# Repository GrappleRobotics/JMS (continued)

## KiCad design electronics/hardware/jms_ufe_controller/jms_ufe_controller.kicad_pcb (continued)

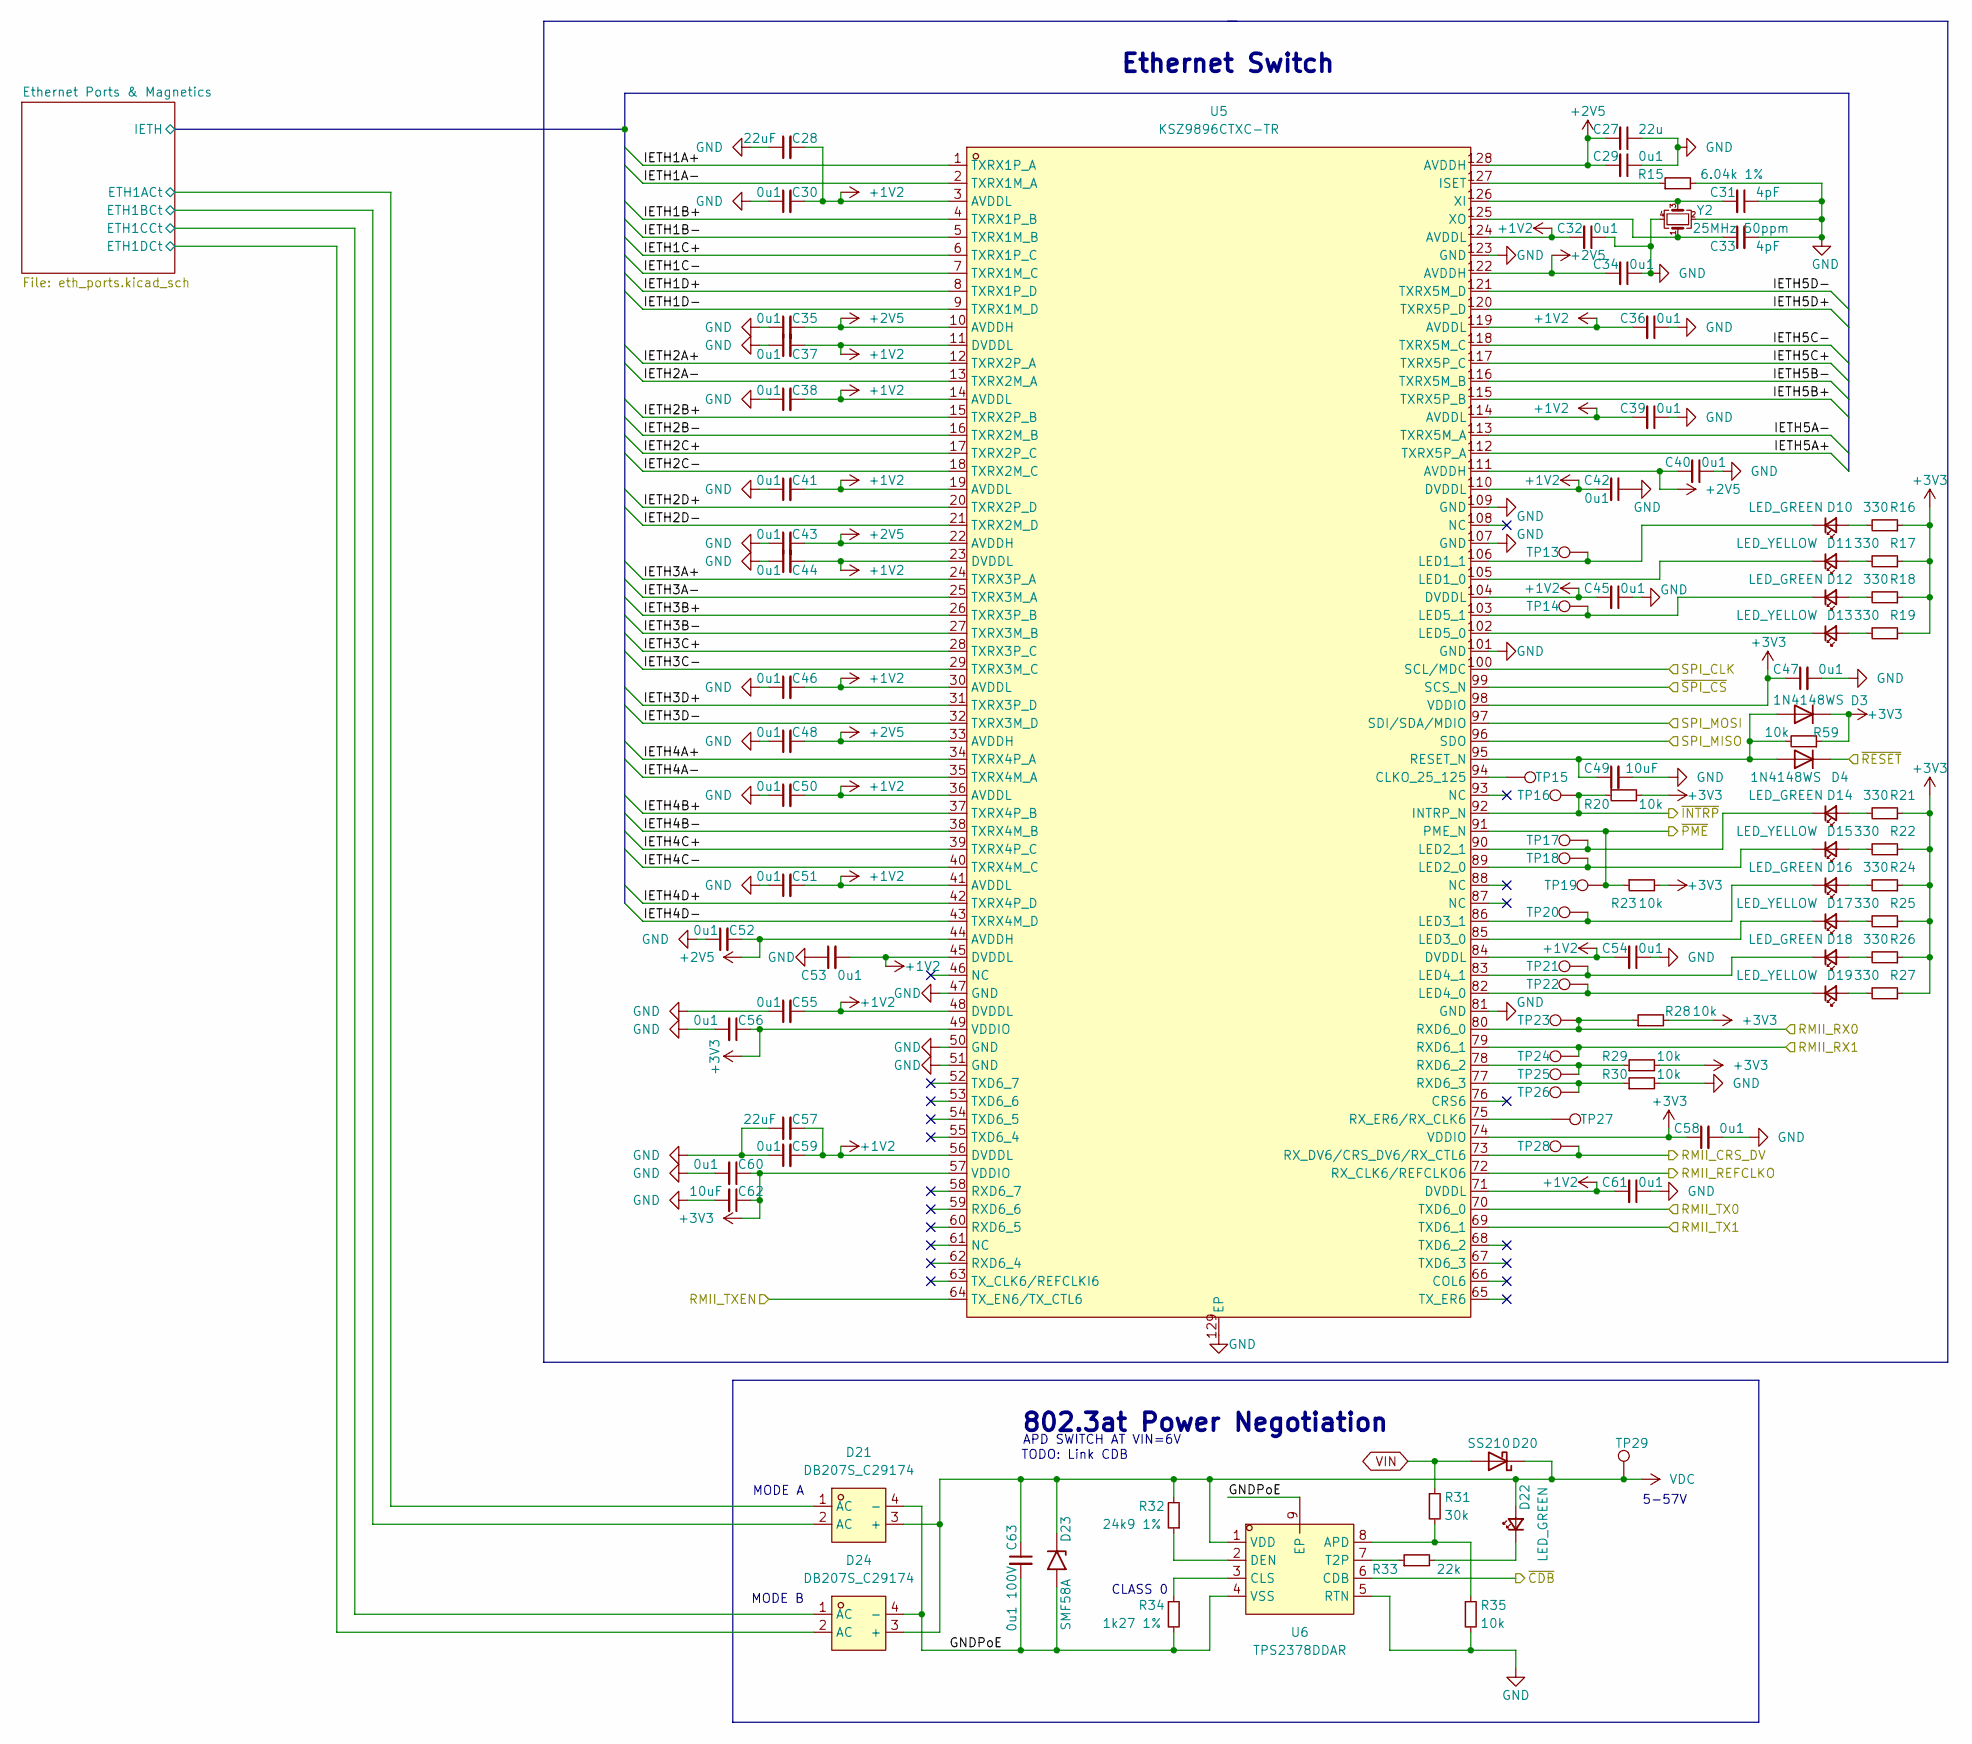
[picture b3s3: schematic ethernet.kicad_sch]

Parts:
C27: 22u; C_0402_1005Metric
C28, C57: 22uF; C_0402_1005Metric
C29, C30, C32, C34, C35, C36, C37, C38, C39, C40, C41, C42, C43, C44, C45, C46, C47, C48, C50, C51, C52, C53, C54, C55, C56, C58, C59, C60, C61: 0u1; C_0402_1005Metric
C31, C33: 4pF; C_0402_1005Metric
C49, C62: 10uF; C_0402_1005Metric
C63: 0u1 100V; C_0805_2012Metric; LCSC C28233
D3, D4: 1N4148WS; D_SOD-323
D10, D12, D14, D16, D18, D22: LED_GREEN; LED_0603_1608Metric; LCSC C72043
D11, D13, D15, D17, D19: LED_YELLOW; LED_0603_1608Metric; LCSC C72038
D20: SS210; D_SMA; LCSC C14996
D21, D24: DB207S_C29174; DBS_L8.4-W6.4-P5.10-LS10.2-TL; LCSC Part C29174
D23: SMF58A; D_SMF
R15: 6.04k 1%; R_0402_1005Metric
R16, R17, R18, R19, R21, R22, R24, R25, R26, R27: 330; R_0402_1005Metric
R20, R23, R28, R29, R30, R35, R59: 10k; R_0402_1005Metric
R31: 30k; R_0402_1005Metric
R32: 24k9 1%; R_0402_1005Metric
R33: 22k; R_0402_1005Metric
R34: 1k27 1%; R_0402_1005Metric
TP13, TP14, TP15, TP16, TP17, TP18, TP19, TP20, TP21, TP22, TP23, TP24, TP25, TP26, TP27, TP28, TP29: TestPoint; TestPoint_Pad_1.5x1.5mm
U5: KSZ9896CTXC-TR; TQFP-128_L14.0-W14.0-P0.40-LS16.0-BL-EP; LCSC Part C631691
U6: TPS2378DDAR; SO-8_L4.9-W3.9-P1.27-LS6.0-BL-EP; LCSC Part C337500
Y2: 25MHz 50ppm; Crystal_SMD_3225-4Pin_3.2x2.5mm; LCSC C9006

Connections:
+1V2: C28.2, C30.2, C32.2, C36.2, C37.2, C38.2, C39.2, C41.2, C42.2, C44.2, C45.2, C46.2, C50.2, C51.2, C53.2, C54.2, C55.2, C57.2, C59.2, C61.2, U5.3 (AVDDL), U5.11 (DVDDL), U5.14 (AVDDL), U5.19 (AVDDL), U5.23 (DVDDL), U5.30 (AVDDL), U5.36 (AVDDL), U5.41 (AVDDL), U5.45 (DVDDL), U5.48 (DVDDL), U5.56 (DVDDL), U5.71 (DVDDL), U5.84 (DVDDL), U5.104 (DVDDL), U5.110 (DVDDL), U5.114 (AVDDL), U5.119 (AVDDL), U5.124 (AVDDL); also elsewhere on the board
+2V5: C27.2, C29.2, C34.2, C35.2, C40.2, C43.2, C48.2, C52.2, U5.10 (AVDDH), U5.22 (AVDDH), U5.33 (AVDDH), U5.44 (AVDDH), U5.111 (AVDDH), U5.122 (AVDDH), U5.128 (AVDDH); also elsewhere on the board
+3V3: C47.1, C56.1, C58.1, C60.1, C62.1, D3.1 (K), R16.1, R17.1, R18.1, R19.1, R20.2, R21.1, R22.1, R23.2, R24.1, R25.1, R26.1, R27.1, R28.2, R29.2, R59.1, U5.49 (VDDIO), U5.57 (VDDIO), U5.74 (VDDIO), U5.98 (VDDIO); also elsewhere on the board
/EH_SPI_SCLK: U5.100 (SCL/MDC)
/ETH_CRS_DV: TP28.1, U5.73 (RX_DV6/CRS_DV6/RX_CTL6); also elsewhere on the board
/ETH_REF_CLK: U5.72 (RX_CLK6/REFCLKO6); also elsewhere on the board
/ETH_RXD0: R28.1, TP23.1, U5.80 (RXD6_0); also elsewhere on the board
/ETH_RXD1: TP24.1, U5.79 (RXD6_1); also elsewhere on the board
/ETH_SPI_CS: U5.99 (SCS_N); also elsewhere on the board
/ETH_SPI_MISO: U5.96 (SDO); also elsewhere on the board
/ETH_SPI_MOSI: U5.97 (SDI/SDA/MDIO); also elsewhere on the board
/ETH_TXD0: U5.70 (TXD6_0); also elsewhere on the board
/ETH_TXD1: U5.69 (TXD6_1); also elsewhere on the board
/ETH_TX_EN: U5.64 (TX_EN6/TX_CTL6); also elsewhere on the board
/ethernet/Ethernet Ports & Magnetics/ETH1ACt: D21.1 (AC); also elsewhere on the board
/ethernet/Ethernet Ports & Magnetics/ETH1BCt: D21.2 (AC); also elsewhere on the board
/ethernet/Ethernet Ports & Magnetics/ETH1CCt: D24.1 (AC); also elsewhere on the board
/ethernet/Ethernet Ports & Magnetics/ETH1DCt: D24.2 (AC); also elsewhere on the board
/ethernet/GNDPoE: C63.2, D21.4 (-), D23.2 (A2), D24.4 (-), R34.2, U6.4 (VSS), U6.9 (EP)
/ethernet/IETH1A+: U5.1 (TXRX1P_A)
/ethernet/IETH1A-: U5.2 (TXRX1M_A)
/ethernet/IETH1B+: U5.4 (TXRX1P_B)
/ethernet/IETH1B-: U5.5 (TXRX1M_B)
/ethernet/IETH1C+: U5.6 (TXRX1P_C)
/ethernet/IETH1C-: U5.7 (TXRX1M_C)
/ethernet/IETH1D+: U5.8 (TXRX1P_D)
/ethernet/IETH1D-: U5.9 (TXRX1M_D)
/ethernet/IETH2A+: U5.12 (TXRX2P_A)
/ethernet/IETH2A-: U5.13 (TXRX2M_A)
/ethernet/IETH2B+: U5.15 (TXRX2P_B)
/ethernet/IETH2B-: U5.16 (TXRX2M_B)
/ethernet/IETH2C+: U5.17 (TXRX2P_C)
/ethernet/IETH2C-: U5.18 (TXRX2M_C)
/ethernet/IETH2D+: U5.20 (TXRX2P_D)
/ethernet/IETH2D-: U5.21 (TXRX2M_D)
/ethernet/IETH3A+: U5.24 (TXRX3P_A)
/ethernet/IETH3A-: U5.25 (TXRX3M_A)
/ethernet/IETH3B+: U5.26 (TXRX3P_B)
/ethernet/IETH3B-: U5.27 (TXRX3M_B)
/ethernet/IETH3C+: U5.28 (TXRX3P_C)
/ethernet/IETH3C-: U5.29 (TXRX3M_C)
/ethernet/IETH3D+: U5.31 (TXRX3P_D)
/ethernet/IETH3D-: U5.32 (TXRX3M_D)
/ethernet/IETH4A+: U5.34 (TXRX4P_A)
/ethernet/IETH4A-: U5.35 (TXRX4M_A)
/ethernet/IETH4B+: U5.37 (TXRX4P_B)
/ethernet/IETH4B-: U5.38 (TXRX4M_B)
/ethernet/IETH4C+: U5.39 (TXRX4P_C)
/ethernet/IETH4C-: U5.40 (TXRX4M_C)
/ethernet/IETH4D+: U5.42 (TXRX4P_D)
/ethernet/IETH4D-: U5.43 (TXRX4M_D)
/ethernet/IETH5A+: U5.112 (TXRX5P_A)
/ethernet/IETH5A-: U5.113 (TXRX5M_A)
/ethernet/IETH5B+: U5.115 (TXRX5P_B)
/ethernet/IETH5B-: U5.116 (TXRX5M_B)
/ethernet/IETH5C+: U5.117 (TXRX5P_C)
/ethernet/IETH5C-: U5.118 (TXRX5M_C)
/ethernet/IETH5D+: U5.120 (TXRX5P_D)
/ethernet/IETH5D-: U5.121 (TXRX5M_D)
/ethernet/~CDB: U6.6 (CDB); also elsewhere on the board
/~ETH_INTERRUPT: R20.1, TP16.1, U5.92 (INTRP_N); also elsewhere on the board
/~ETH_PME: R23.1, TP19.1, U5.91 (PME_N); also elsewhere on the board
/~ETH_RESET: D4.1 (K); also elsewhere on the board
GND: C27.1, C28.1, C29.1, C30.1, C31.1, C32.1, C33.2, C34.1, C35.1, C36.1, C37.1, C38.1, C39.1, C40.1, C41.1, C42.1, C43.1, C44.1, C45.1, C46.1, C47.2, C48.1, C49.2, C50.1, C51.1, C52.1, C53.1, C54.1, C55.1, C56.2, C57.1, C58.2, C59.1, C60.2, C61.1, C62.2, R15.2, R30.2, R35.2, U5.47 (GND), U5.50 (GND), U5.51 (GND), U5.81 (GND), U5.101 (GND), U5.107 (GND), U5.109 (GND), U5.123 (GND), U5.129 (EP), U6.5 (RTN), Y2.2, Y2.4; also elsewhere on the board
unnamed: C31.2, U5.126 (XI), Y2.3
unnamed: C33.1, U5.125 (XO), Y2.1
unnamed: C49.1, D3.2 (A), D4.2 (A), R59.2, U5.95 (RESET_N)
unnamed: D10.1 (K), TP13.1, U5.106 (LED1_1)
unnamed: D10.2 (A), R16.2
unnamed: D11.1 (K), U5.105 (LED1_0)
unnamed: D11.2 (A), R17.2
unnamed: D12.1 (K), TP14.1, U5.103 (LED5_1)
unnamed: D12.2 (A), R18.2
unnamed: D13.1 (K), U5.102 (LED5_0)
unnamed: D13.2 (A), R19.2
unnamed: D14.1 (K), TP17.1, U5.90 (LED2_1)
unnamed: D14.2 (A), R21.2
unnamed: D15.1 (K), TP18.1, U5.89 (LED2_0)
unnamed: D15.2 (A), R22.2
unnamed: D16.1 (K), TP20.1, U5.86 (LED3_1)
unnamed: D16.2 (A), R24.2
unnamed: D17.1 (K), U5.85 (LED3_0)
unnamed: D17.2 (A), R25.2
unnamed: D18.1 (K), TP21.1, U5.83 (LED4_1)
unnamed: D18.2 (A), R26.2
unnamed: D19.1 (K), TP22.1, U5.82 (LED4_0)
unnamed: D19.2 (A), R27.2
unnamed: D22.1 (K), R33.2
unnamed: R15.1, U5.127 (ISET)
unnamed: R29.1, TP25.1, U5.78 (RXD6_2)
unnamed: R30.1, TP26.1, U5.77 (RXD6_3)
unnamed: R31.2, R35.1, U6.8 (APD)
unnamed: R32.1, U6.2 (DEN)
unnamed: R33.1, U6.7 (T2P)
unnamed: R34.1, U6.3 (CLS)
unnamed: TP15.1, U5.94 (CLKO_25_125)
unnamed: TP27.1, U5.75 (RX_ER6/RX_CLK6)
VDC: C63.1, D20.1 (K), D21.3 (+), D22.2 (A), D23.1 (A1), D24.3 (+), R32.2, TP29.1, U6.1 (VDD); also elsewhere on the board
VIN: D20.2 (A), R31.1; also elsewhere on the board

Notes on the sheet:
Ethernet Switch
5-57V
TODO: Link CDB
MODE B
MODE A
APD SWITCH AT VIN=6V
CLASS 0
802.3at Power Negotiation

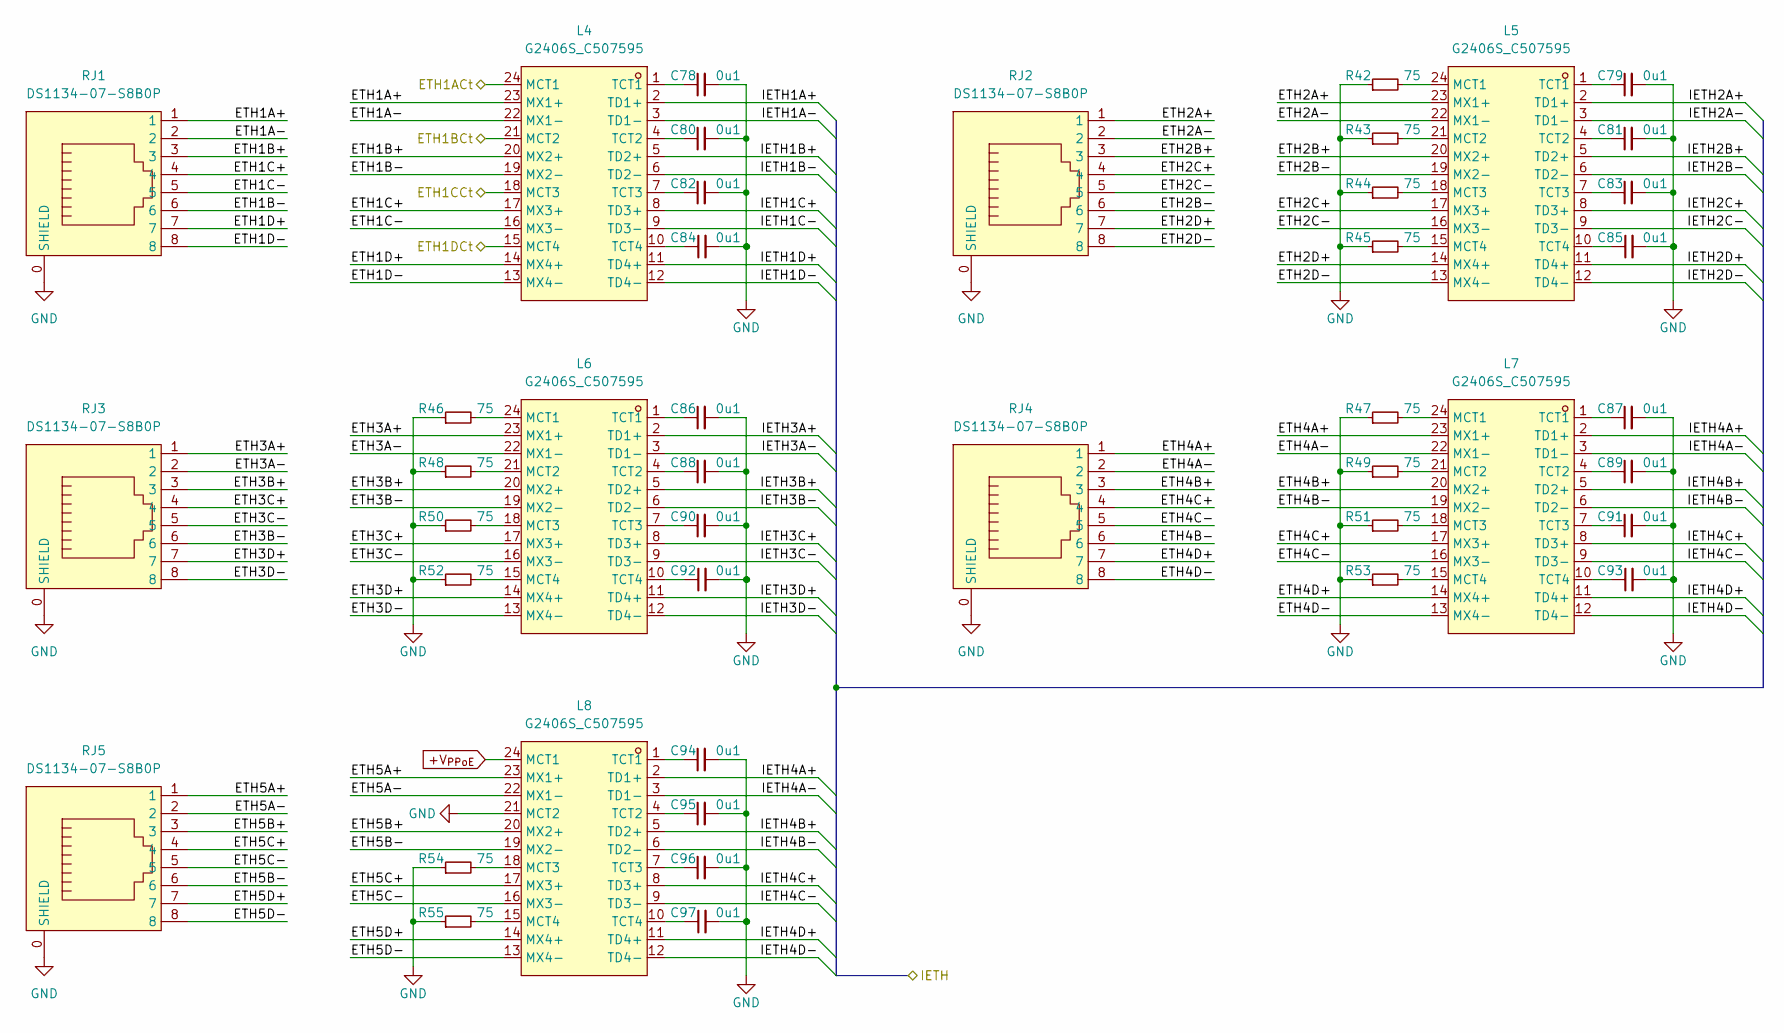
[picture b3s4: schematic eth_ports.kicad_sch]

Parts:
C78, C79, C80, C81, C82, C83, C84, C85, C86, C87, C88, C89, C90, C91, C92, C93, C94, C95, C96, C97: 0u1; C_0402_1005Metric
L4, L5, L6, L7, L8: G2406S_C507595; SMD-24_L15.1-W7.1-P1.00-LS10.0-BL; LCSC Part C507595
R42, R43, R44, R45, R46, R47, R48, R49, R50, R51, R52, R53, R54, R55: 75; R_0402_1005Metric
RJ1, RJ2, RJ3, RJ4, RJ5: DS1134-07-S8B0P; RJ45-TH_DS1134-07-S8B0P; LCSC Part C86579

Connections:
+V_{PPoE}: L8.24 (MCT1); also elsewhere on the board
/ethernet/Ethernet Ports & Magnetics/ETH1A+: L4.23 (MX1+), RJ1.1
/ethernet/Ethernet Ports & Magnetics/ETH1A-: L4.22 (MX1-), RJ1.2
/ethernet/Ethernet Ports & Magnetics/ETH1ACt: L4.24 (MCT1); also elsewhere on the board
/ethernet/Ethernet Ports & Magnetics/ETH1B+: L4.20 (MX2+), RJ1.3
/ethernet/Ethernet Ports & Magnetics/ETH1B-: L4.19 (MX2-), RJ1.6
/ethernet/Ethernet Ports & Magnetics/ETH1BCt: L4.21 (MCT2); also elsewhere on the board
/ethernet/Ethernet Ports & Magnetics/ETH1C+: L4.17 (MX3+), RJ1.4
/ethernet/Ethernet Ports & Magnetics/ETH1C-: L4.16 (MX3-), RJ1.5
/ethernet/Ethernet Ports & Magnetics/ETH1CCt: L4.18 (MCT3); also elsewhere on the board
/ethernet/Ethernet Ports & Magnetics/ETH1D+: L4.14 (MX4+), RJ1.7
/ethernet/Ethernet Ports & Magnetics/ETH1D-: L4.13 (MX4-), RJ1.8
/ethernet/Ethernet Ports & Magnetics/ETH1DCt: L4.15 (MCT4); also elsewhere on the board
/ethernet/Ethernet Ports & Magnetics/ETH2A+: L5.23 (MX1+), RJ2.1
/ethernet/Ethernet Ports & Magnetics/ETH2A-: L5.22 (MX1-), RJ2.2
/ethernet/Ethernet Ports & Magnetics/ETH2B+: L5.20 (MX2+), RJ2.3
/ethernet/Ethernet Ports & Magnetics/ETH2B-: L5.19 (MX2-), RJ2.6
/ethernet/Ethernet Ports & Magnetics/ETH2C+: L5.17 (MX3+), RJ2.4
/ethernet/Ethernet Ports & Magnetics/ETH2C-: L5.16 (MX3-), RJ2.5
/ethernet/Ethernet Ports & Magnetics/ETH2D+: L5.14 (MX4+), RJ2.7
/ethernet/Ethernet Ports & Magnetics/ETH2D-: L5.13 (MX4-), RJ2.8
/ethernet/Ethernet Ports & Magnetics/ETH3A+: L6.23 (MX1+), RJ3.1
/ethernet/Ethernet Ports & Magnetics/ETH3A-: L6.22 (MX1-), RJ3.2
/ethernet/Ethernet Ports & Magnetics/ETH3B+: L6.20 (MX2+), RJ3.3
/ethernet/Ethernet Ports & Magnetics/ETH3B-: L6.19 (MX2-), RJ3.6
/ethernet/Ethernet Ports & Magnetics/ETH3C+: L6.17 (MX3+), RJ3.4
/ethernet/Ethernet Ports & Magnetics/ETH3C-: L6.16 (MX3-), RJ3.5
/ethernet/Ethernet Ports & Magnetics/ETH3D+: L6.14 (MX4+), RJ3.7
/ethernet/Ethernet Ports & Magnetics/ETH3D-: L6.13 (MX4-), RJ3.8
/ethernet/Ethernet Ports & Magnetics/ETH4A+: L7.23 (MX1+), RJ4.1
/ethernet/Ethernet Ports & Magnetics/ETH4A-: L7.22 (MX1-), RJ4.2
/ethernet/Ethernet Ports & Magnetics/ETH4B+: L7.20 (MX2+), RJ4.3
/ethernet/Ethernet Ports & Magnetics/ETH4B-: L7.19 (MX2-), RJ4.6
/ethernet/Ethernet Ports & Magnetics/ETH4C+: L7.17 (MX3+), RJ4.4
/ethernet/Ethernet Ports & Magnetics/ETH4C-: L7.16 (MX3-), RJ4.5
/ethernet/Ethernet Ports & Magnetics/ETH4D+: L7.14 (MX4+), RJ4.7
/ethernet/Ethernet Ports & Magnetics/ETH4D-: L7.13 (MX4-), RJ4.8
/ethernet/Ethernet Ports & Magnetics/ETH5A+: L8.23 (MX1+), RJ5.1
/ethernet/Ethernet Ports & Magnetics/ETH5A-: L8.22 (MX1-), RJ5.2
/ethernet/Ethernet Ports & Magnetics/ETH5B+: L8.20 (MX2+), RJ5.3
/ethernet/Ethernet Ports & Magnetics/ETH5B-: L8.19 (MX2-), RJ5.6
/ethernet/Ethernet Ports & Magnetics/ETH5C+: L8.17 (MX3+), RJ5.4
/ethernet/Ethernet Ports & Magnetics/ETH5C-: L8.16 (MX3-), RJ5.5
/ethernet/Ethernet Ports & Magnetics/ETH5D+: L8.14 (MX4+), RJ5.7
/ethernet/Ethernet Ports & Magnetics/ETH5D-: L8.13 (MX4-), RJ5.8
/ethernet/Ethernet Ports & Magnetics/IETH1A+: L4.2 (TD1+)
/ethernet/Ethernet Ports & Magnetics/IETH1A-: L4.3 (TD1-)
/ethernet/Ethernet Ports & Magnetics/IETH1B+: L4.5 (TD2+)
/ethernet/Ethernet Ports & Magnetics/IETH1B-: L4.6 (TD2-)
/ethernet/Ethernet Ports & Magnetics/IETH1C+: L4.8 (TD3+)
/ethernet/Ethernet Ports & Magnetics/IETH1C-: L4.9 (TD3-)
/ethernet/Ethernet Ports & Magnetics/IETH1D+: L4.11 (TD4+)
/ethernet/Ethernet Ports & Magnetics/IETH1D-: L4.12 (TD4-)
/ethernet/Ethernet Ports & Magnetics/IETH2A+: L5.2 (TD1+)
/ethernet/Ethernet Ports & Magnetics/IETH2A-: L5.3 (TD1-)
/ethernet/Ethernet Ports & Magnetics/IETH2B+: L5.5 (TD2+)
/ethernet/Ethernet Ports & Magnetics/IETH2B-: L5.6 (TD2-)
/ethernet/Ethernet Ports & Magnetics/IETH2C+: L5.8 (TD3+)
/ethernet/Ethernet Ports & Magnetics/IETH2C-: L5.9 (TD3-)
/ethernet/Ethernet Ports & Magnetics/IETH2D+: L5.11 (TD4+)
/ethernet/Ethernet Ports & Magnetics/IETH2D-: L5.12 (TD4-)
/ethernet/Ethernet Ports & Magnetics/IETH3A+: L6.2 (TD1+)
/ethernet/Ethernet Ports & Magnetics/IETH3A-: L6.3 (TD1-)
/ethernet/Ethernet Ports & Magnetics/IETH3B+: L6.5 (TD2+)
/ethernet/Ethernet Ports & Magnetics/IETH3B-: L6.6 (TD2-)
/ethernet/Ethernet Ports & Magnetics/IETH3C+: L6.8 (TD3+)
/ethernet/Ethernet Ports & Magnetics/IETH3C-: L6.9 (TD3-)
/ethernet/Ethernet Ports & Magnetics/IETH3D+: L6.11 (TD4+)
/ethernet/Ethernet Ports & Magnetics/IETH3D-: L6.12 (TD4-)
/ethernet/Ethernet Ports & Magnetics/IETH4A+: L7.2 (TD1+), L8.2 (TD1+)
/ethernet/Ethernet Ports & Magnetics/IETH4A-: L7.3 (TD1-), L8.3 (TD1-)
/ethernet/Ethernet Ports & Magnetics/IETH4B+: L7.5 (TD2+), L8.5 (TD2+)
/ethernet/Ethernet Ports & Magnetics/IETH4B-: L7.6 (TD2-), L8.6 (TD2-)
/ethernet/Ethernet Ports & Magnetics/IETH4C+: L7.8 (TD3+), L8.8 (TD3+)
/ethernet/Ethernet Ports & Magnetics/IETH4C-: L7.9 (TD3-), L8.9 (TD3-)
/ethernet/Ethernet Ports & Magnetics/IETH4D+: L7.11 (TD4+), L8.11 (TD4+)
/ethernet/Ethernet Ports & Magnetics/IETH4D-: L7.12 (TD4-), L8.12 (TD4-)
GND: C78.2, C79.2, C80.2, C81.2, C82.2, C83.2, C84.2, C85.2, C86.2, C87.2, C88.2, C89.2, C90.2, C91.2, C92.2, C93.2, C94.2, C95.2, C96.2, C97.2, L8.21 (MCT2), R42.1, R43.1, R44.1, R45.1, R46.1, R47.1, R48.1, R49.1, R50.1, R51.1, R52.1, R53.1, R54.1, R55.1, RJ1.0 (SHIELD), RJ2.0 (SHIELD), RJ3.0 (SHIELD), RJ4.0 (SHIELD), RJ5.0 (SHIELD); also elsewhere on the board
unnamed: C78.1, L4.1 (TCT1)
unnamed: C79.1, L5.1 (TCT1)
unnamed: C80.1, L4.4 (TCT2)
unnamed: C81.1, L5.4 (TCT2)
unnamed: C82.1, L4.7 (TCT3)
unnamed: C83.1, L5.7 (TCT3)
unnamed: C86.1, L6.1 (TCT1)
unnamed: C87.1, L7.1 (TCT1)
unnamed: C88.1, L6.4 (TCT2)
unnamed: C89.1, L7.4 (TCT2)
unnamed: C90.1, L6.7 (TCT3)
unnamed: C91.1, L7.7 (TCT3)
unnamed: C94.1, L8.1 (TCT1)
unnamed: C95.1, L8.4 (TCT2)
unnamed: C96.1, L8.7 (TCT3)
unnamed: L5.15 (MCT4), R45.2
unnamed: L5.18 (MCT3), R44.2
unnamed: L5.21 (MCT2), R43.2
unnamed: L5.24 (MCT1), R42.2
unnamed: L6.15 (MCT4), R52.2
unnamed: L6.18 (MCT3), R50.2
unnamed: L6.21 (MCT2), R48.2
unnamed: L6.24 (MCT1), R46.2
unnamed: L7.15 (MCT4), R53.2
unnamed: L7.18 (MCT3), R51.2
unnamed: L7.21 (MCT2), R49.2
unnamed: L7.24 (MCT1), R47.2
unnamed: L8.15 (MCT4), R55.2
unnamed: L8.18 (MCT3), R54.2

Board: 4 copper layers, 250 parts (0 on the bottom side), 261 nets, no tracks yet.

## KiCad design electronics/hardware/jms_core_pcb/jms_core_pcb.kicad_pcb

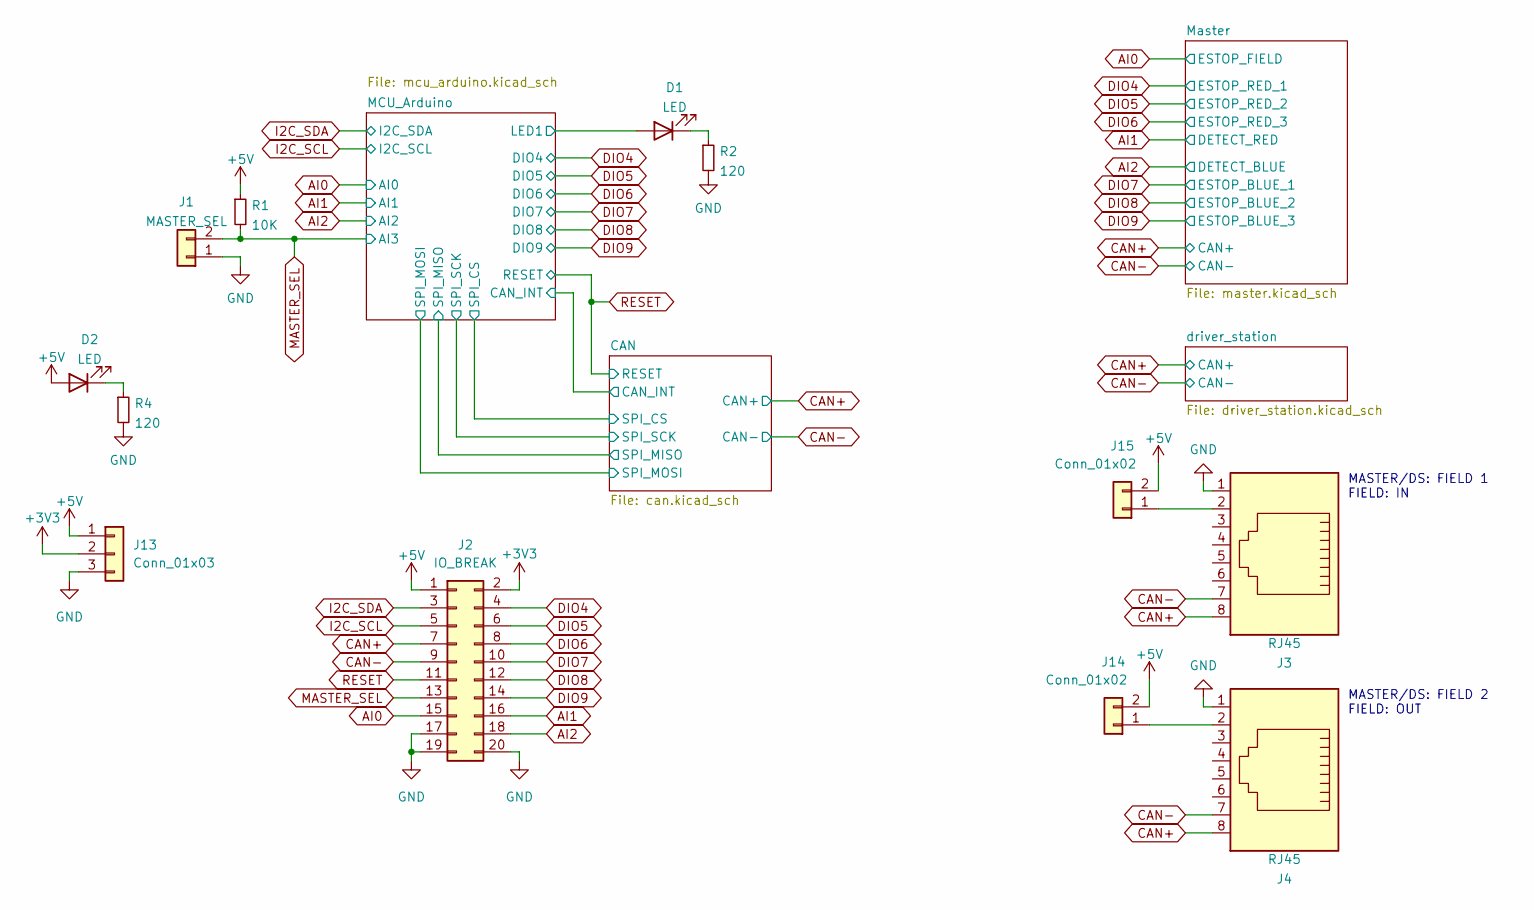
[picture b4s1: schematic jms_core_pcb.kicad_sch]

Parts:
D1, D2: LED; LED_D3.0mm
J1: MASTER_SEL; PinHeader_1x02_P2.54mm_Vertical
J2: IO_BREAK; PinHeader_2x10_P2.54mm_Vertical
J3, J4: RJ45; RJ45_Amphenol_54602-x08_Horizontal
J13: Conn_01x03; TerminalBlock_Phoenix_MKDS-1,5-3-5.08_1x03_P5.08mm_Horizont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
J14, J15: Conn_01x02; PinHeader_1x02_P2.54mm_Vertical
R1: 10K; R_Axial_DIN0207_L6.3mm_D2.5mm_P7.62mm_Horizontal
R2, R4: 120; R_Axial_DIN0207_L6.3mm_D2.5mm_P7.62mm_Horizontal

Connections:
+3V3: J2.2, J13.2; also elsewhere on the board
+5V: D2.2 (A), J2.1, J13.1, J14.2, J15.2, R1.1; also elsewhere on the board
/MCU_Arduino/LED1: D1.2 (A); also elsewhere on the board
AI0: J2.15; also elsewhere on the board
AI1: J2.16; also elsewhere on the board
AI2: J2.18; also elsewhere on the board
CAN+: J2.7, J3.8, J4.8; also elsewhere on the board
CAN-: J2.9, J3.7, J4.7; also elsewhere on the board
DIO4: J2.4; also elsewhere on the board
DIO5: J2.6; also elsewhere on the board
DIO6: J2.8; also elsewhere on the board
DIO7: J2.10; also elsewhere on the board
DIO8: J2.12; also elsewhere on the board
DIO9: J2.14; also elsewhere on the board
GND: J1.1, J2.17, J2.19, J2.20, J3.1, J4.1, J13.3, R2.2, R4.2; also elsewhere on the board
I2C_SCL: J2.5; also elsewhere on the board
I2C_SDA: J2.3; also elsewhere on the board
MASTER_SEL: J1.2, J2.13, R1.2; also elsewhere on the board
unnamed: D1.1 (K), R2.1
unnamed: D2.1 (K), R4.1
unnamed: J3.2, J15.1
unnamed: J4.2, J14.1
RESET: J2.11; also elsewhere on the board

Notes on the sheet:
MASTER/DS: FIELD 2 FIELD: OUT
MASTER/DS: FIELD 1 FIELD: IN

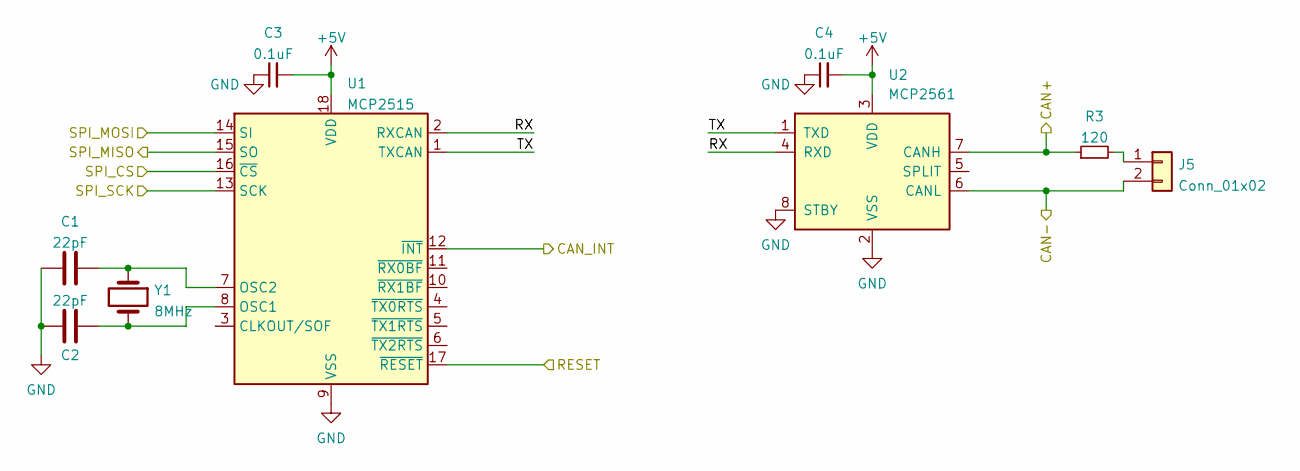
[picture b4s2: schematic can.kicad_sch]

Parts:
C1, C2: 22pF; C_Disc_D5.0mm_W2.5mm_P5.00mm
C3, C4: 0.1uF; C_Disc_D5.0mm_W2.5mm_P5.00mm
J5: Conn_01x02; PinHeader_1x02_P2.54mm_Vertical
R3: 120; R_Axial_DIN0207_L6.3mm_D2.5mm_P7.62mm_Horizontal
U1: MCP2515; SOIC-18W_7.5x11.6mm_P1.27mm
U2: MCP2561; DIP-8_W7.62mm
Y1: 8MHz; Crystal_HC49-U_Vertical

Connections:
+5V: C3.2, C4.2, U1.18 (VDD), U2.3 (VDD); also elsewhere on the board
/CAN/CAN_INT: U1.12 (~INT); also elsewhere on the board
/CAN/RX: U1.2 (RXCAN), U2.4 (RXD)
/CAN/SPI_CS: U1.16 (~CS); also elsewhere on the board
/CAN/SPI_MISO: U1.15 (SO); also elsewhere on the board
/CAN/SPI_MOSI: U1.14 (SI); also elsewhere on the board
/CAN/SPI_SCK: U1.13 (SCK); also elsewhere on the board
/CAN/TX: U1.1 (TXCAN), U2.1 (TXD)
CAN+: R3.1, U2.7 (CANH); also elsewhere on the board
CAN-: J5.2, U2.6 (CANL); also elsewhere on the board
GND: C1.1, C2.1, C3.1, C4.1, U1.9 (VSS), U2.2 (VSS), U2.8 (STBY); also elsewhere on the board
unnamed: C1.2, U1.7 (OSC2), Y1.1
unnamed: C2.2, U1.8 (OSC1), Y1.2
unnamed: J5.1, R3.2
RESET: U1.17 (~RESET); also elsewhere on the board

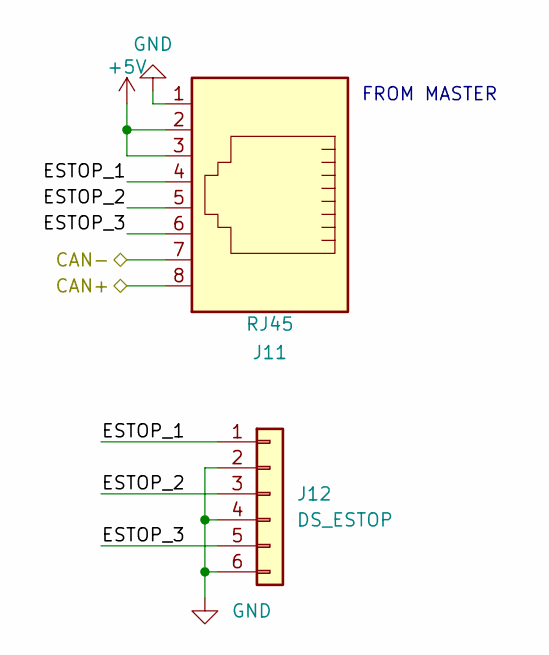
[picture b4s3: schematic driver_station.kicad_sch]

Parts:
J11: RJ45; RJ45_Amphenol_54602-x08_Horizontal
J12: DS_ESTOP; TerminalBlock_Phoenix_MKDS-1,5-6-5.08_1x06_P5.08mm_Horizont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

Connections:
+5V: J11.2, J11.3; also elsewhere on the board
/driver_station/ESTOP_1: J11.4, J12.1
/driver_station/ESTOP_2: J11.5, J12.3
/driver_station/ESTOP_3: J11.6, J12.5
CAN+: J11.8; also elsewhere on the board
CAN-: J11.7; also elsewhere on the board
GND: J11.1, J12.2, J12.4, J12.6; also elsewhere on the board

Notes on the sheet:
FROM MASTER

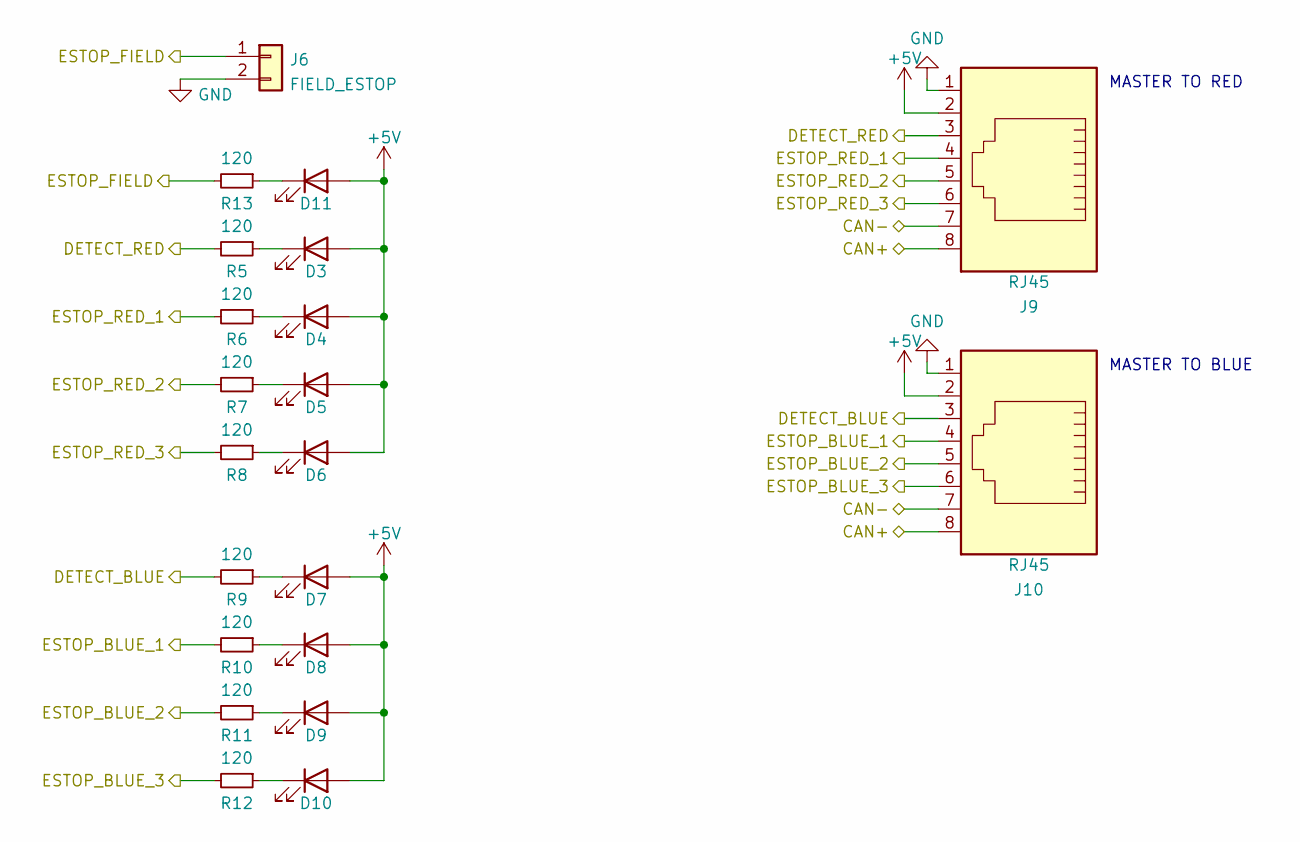
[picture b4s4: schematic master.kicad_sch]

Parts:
D3, D4, D5, D6, D7, D8, D9, D10, D11: LED; LED_D3.0mm
J6: FIELD_ESTOP; TerminalBlock_Phoenix_MKDS-1,5-2-5.08_1x02_P5.08mm_Horizont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
J9, J10: RJ45; RJ45_Amphenol_54602-x08_Horizontal
R5, R6, R7, R8, R9, R10, R11, R12, R13: 120; R_Axial_DIN0207_L6.3mm_D2.5mm_P7.62mm_Horizontal

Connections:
+5V: D3.2 (A), D4.2 (A), D5.2 (A), D6.2 (A), D7.2 (A), D8.2 (A), D9.2 (A), D10.2 (A), D11.2 (A), J9.2, J10.2; also elsewhere on the board
AI0: J6.1, R13.2; also elsewhere on the board
AI1: J9.3, R5.2; also elsewhere on the board
AI2: J10.3, R9.2; also elsewhere on the board
CAN+: J9.8, J10.8; also elsewhere on the board
CAN-: J9.7, J10.7; also elsewhere on the board
DIO4: J9.4, R6.2; also elsewhere on the board
DIO5: J9.5, R7.2; also elsewhere on the board
DIO6: J9.6, R8.2; also elsewhere on the board
DIO7: J10.4, R10.2; also elsewhere on the board
DIO8: J10.5, R11.2; also elsewhere on the board
DIO9: J10.6, R12.2; also elsewhere on the board
GND: J6.2, J9.1, J10.1; also elsewhere on the board
unnamed: D3.1 (K), R5.1
unnamed: D4.1 (K), R6.1
unnamed: D5.1 (K), R7.1
unnamed: D6.1 (K), R8.1
unnamed: D7.1 (K), R9.1
unnamed: D8.1 (K), R10.1
unnamed: D9.1 (K), R11.1
unnamed: D10.1 (K), R12.1
unnamed: D11.1 (K), R13.1

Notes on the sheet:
MASTER TO RED
MASTER TO BLUE

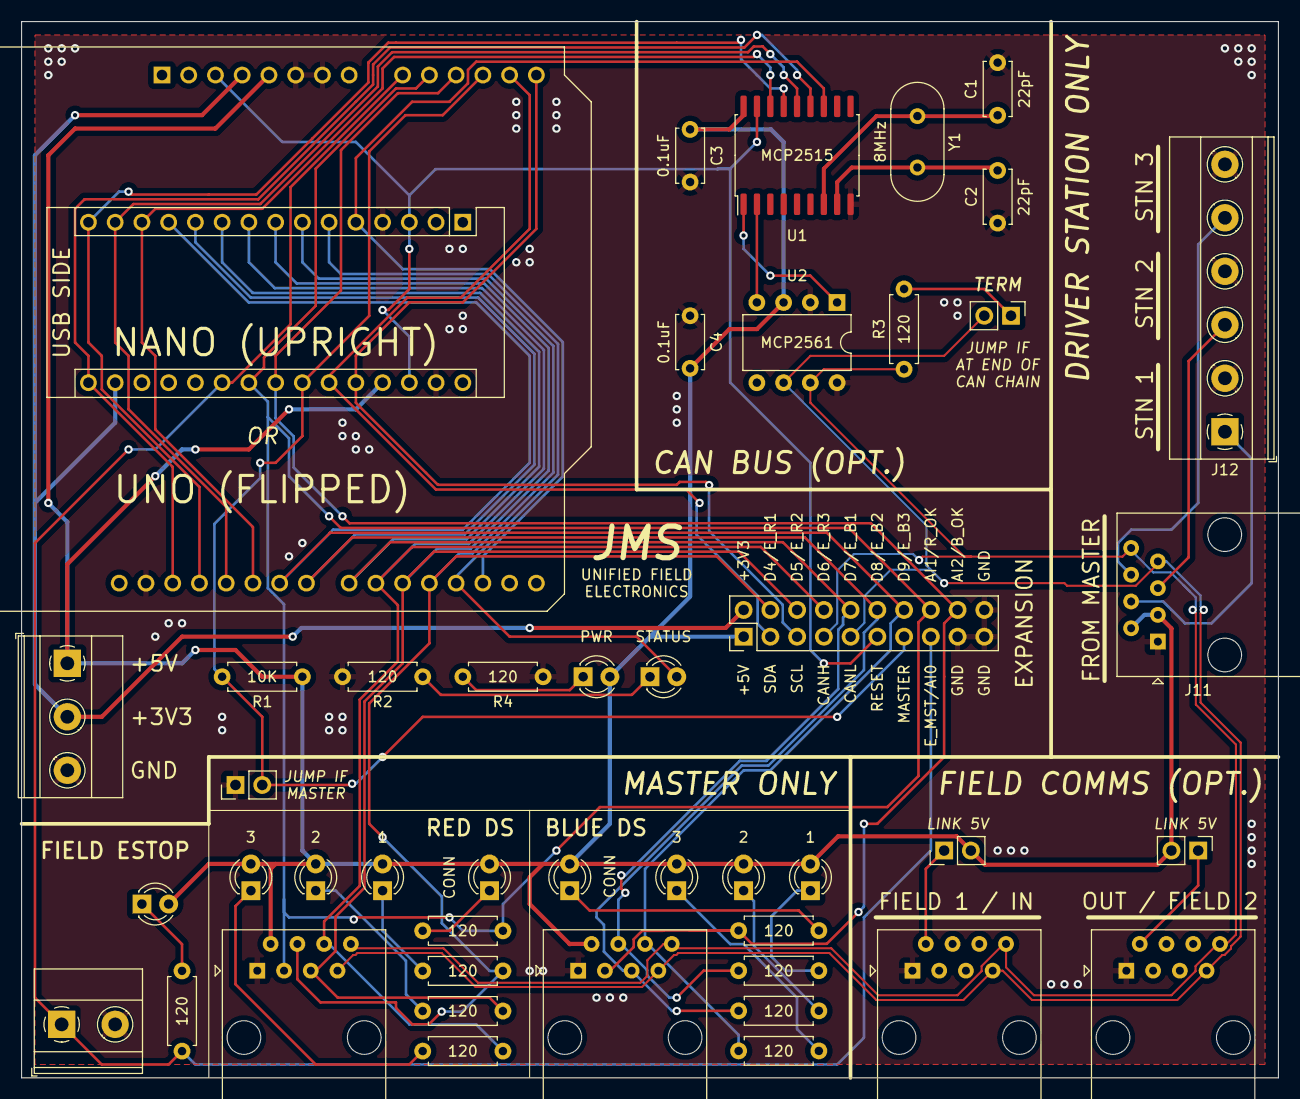
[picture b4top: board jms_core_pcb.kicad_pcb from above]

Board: 2 copper layers, 119.4 x 100.3 mm, 46 parts (0 on the bottom side), 45 nets.

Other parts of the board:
A1: Arduino_UNO_R2
A2: Arduino_Nano_v3.x; Arduino_Nano

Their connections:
+3V3: A1.4 (3V3), A2.17 (3V3); also elsewhere on the board
+5V: A1.5 (+5V), A2.27 (+5V); also elsewhere on the board
/CAN/CAN_INT: A1.17 (D2), A2.5 (D2); also elsewhere on the board
/CAN/SPI_CS: A1.25 (D10), A2.13 (D10); also elsewhere on the board
/CAN/SPI_MISO: A1.27 (D12), A2.15 (D12); also elsewhere on the board
/CAN/SPI_MOSI: A1.26 (D11), A2.14 (D11); also elsewhere on the board
/CAN/SPI_SCK: A1.28 (D13), A2.16 (D13); also elsewhere on the board
/MCU_Arduino/LED1: A1.18 (D3), A2.6 (D3); also elsewhere on the board
AI0: A1.9 (A0), A2.21 (A2); also elsewhere on the board
AI1: A1.10 (A1), A2.22 (A3); also elsewhere on the board
AI2: A1.11 (A2), A2.23 (A4); also elsewhere on the board
DIO4: A1.19 (D4), A2.7 (D4); also elsewhere on the board
DIO5: A1.20 (D5), A2.8 (D5); also elsewhere on the board
DIO6: A1.21 (D6), A2.9 (D6); also elsewhere on the board
DIO7: A1.22 (D7), A2.10 (D7); also elsewhere on the board
DIO8: A1.23 (D8), A2.11 (D8); also elsewhere on the board
DIO9: A1.24 (D9), A2.12 (D9); also elsewhere on the board
GND: A1.6 (GND), A1.7 (GND), A1.29 (GND), A2.4 (GND), A2.29 (GND); also elsewhere on the board
I2C_SCL: A1.14 (SCL/A5), A2.26 (A7); also elsewhere on the board
I2C_SDA: A1.13 (SDA/A4), A2.25 (A6); also elsewhere on the board
MASTER_SEL: A1.12 (A3), A2.24 (A5); also elsewhere on the board
RESET: A1.3 (~RESET), A2.3 (~RESET), A2.28 (~RESET); also elsewhere on the board
